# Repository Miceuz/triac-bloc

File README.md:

triac-bloc
==========

Version 3 plan:
* use fl5150mx
* rs845
* filtering and protection 

A universal power block based on triac. In essence this is a solid state relay that can be augmented with some bells and whistles. 

Bells and whistles:
 * Attiyny44 MCU on board
 * I2C interface
 * Optional filtering
 * Optional snubber network
 * maximum power - 6kW
 * zero crossing detection
 * firmware supprots linear output power control
 * phase shift dimmer mode
 * switch at zero-crossing mode
 * “low level” zero-crossing signal output
 * “low level” triac trigger signal input
 * 4 spare MCU pins available for additional features
 * open source hardware and firmware

More info available at: http://wemakethings.net/2013/10/27/triac-bloc/

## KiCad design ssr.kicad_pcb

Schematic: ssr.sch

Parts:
C1: 10nF 400V; C_Rect_L13_W4_P10; PartNo R46KF210050N0K
C2: 47nF 400V; C_Rect_L13_W6_H12_P10; PartNo R46KI24705001K
C3: 100nF 400V; C_Rect_L13_W6_H12_P10; PartNo BFC233922104
C4: 1u; C_0603; PartNo ?
C5: 100uF; Elko_vert_11.2x7.5mm_RM2.5_CopperClear; PartNo ?
C6: C; C_0603; PartNo ?
C7: 10u; Elko_vert_11.2x7.5mm_RM2.5_CopperClear; PartNo ?
C8: 1n; c_0603; PartNo ?
C9: 1u; C_0603
CON1: AVR-ISP-6; Pin_Header_Straight_2x03_Pitch2.54mm; PartNo ?
CONN10: CONN_01X06; Pin_Header_Straight_1x06_Pitch2.54mm; PartNo ?
D1, D2: LED; SM0805; PartNo ?
D3, D5, D6, D7: 1N4148; SOD-323; PartNo ?
D4: 1N4148; SOD-323; PartNo 1N4148WS
F1: FUSE; Fuseholder5x20_horiz_open_universal_Type-III; PartNo 0314030.MXP
IC2: ATTINY441-SSU; SOIC-14_3.9x8.7mm_Pitch1.27mm; PartNo ATTINY441-SSU
J1: 240VAC; Molex_MiniFit-JR-5556-02A_2x01x4.20mm_Straight; PartNo ?
J2: LOAD; Molex_MiniFit-JR-5556-02A_2x01x4.20mm_Straight; PartNo ?
L1: 40-100uH; Choke_Toroid_8x16mm_Vertical; PartNo ?
P1, P6: CONN_4; connect-SC-04; PartNo ?
Q1, Q2: 2N3904; sot23; PartNo MMBT3904-7-F
R1: 360R; R15.5x6; PartNo CFR200J390R
R2: 4.7k; r_0603; PartNo ?
R3: 39; RC05; PartNo MFP1-39R JI
R4, R15: 1k; r_0603; PartNo ?
R5: 22k; r_0603; PartNo ?
R6: 470R; R12x5.2; PartNo CFR100J470R
R7, R9: 10k; r_0603; PartNo ?
R8: 510k; RC05; PartNo MF50 510K
R10: 200; r_0603; PartNo ?
R11, R12: 220; r_0603; PartNo ?
R13, R14: 220k; r_2010; PartNo MCPWR10FTEQ2203
R16: 0R; r_0603; PartNo ?
R17: 120; r_0603; PartNo ?
U1: MOC-3052; optocoupler-2-DIL06; PartNo MOC3052M
U2: BTA41; top3; PartNo BTA41-600BRG
U3: 4N35; mdip_6; PartNo 4N35S-M..
U4: SP3485EN; SOIC-8_3.9x4.9mm_Pitch1.27mm; PartNo SP485EMN-L
VR1: VR; varistor-S05K40; PartNo MCSR431K07DS

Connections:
/FIRE: U1.4 (S2), U2.3
/LINE: F1.1, R3.2, R6.2, R13.2, U2.2, VR1.1
/LOAD: C1.2, C2.2, L1.1, U2.1
/LOAD-FILTERED: C3.2, J2.1, L1.2, R8.2
/MISO: CON1.1, IC2.8 ((PCINT5/MISO/TXD1/T2/TOCC4/ACO0/ADC5)PA5), R12.1
/MOSI: CON1.4, IC2.7 ((PCINT6/MOSI/SDA/XCK1/TOCC5/ACO1/ADC6)P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), R11.1
/NEUTRAL: J1.2, J2.2, R14.2, VR1.2
/RESET: CON1.5, IC2.4 ((PCINT11/dW/~RESET~/ADC9)PB3), R7.1
/RS485-A: P6.3, R16.1, U4.6 (A)
/RS485-B: P6.2, R17.2, U4.7 (B)
/RX: IC2.5 ((PCINT10/RXD0/ICP2/CLKO/TOCC7/ADC8)PB2), U4.1 (RO)
/SCK: CON1.3, IC2.9 ((PCINT4/SCK/SCL/RXD1/T1/TOCC3/AIN11/ADC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), U4.2 (~RE~), U4.3 (DE)
/TX: IC2.6 ((PCINT7/~SS~/TXD0/ICP1/TOCC6/ADC7)PA7), U4.4 (DI)
GND: C4.2, C5.2, C6.2, C9.2, CON1.6, CONN10.1, D1.2 (K), D2.2 (K), IC2.14 (GND), P1.1, P6.4, Q1.3 (E), R9.2, U3.4, U4.5 (GND)
unnamed: C1.1, R3.1
unnamed: C2.1, R1.2, R6.1
unnamed: C3.1, F1.2, J1.1, R8.1
unnamed: C7.1, D4.1 (K), D5.1 (K), R4.2, R5.2
unnamed: C7.2, D3.2 (A), Q2.3 (E)
unnamed: C8.1, D4.2 (A), D7.1 (K), R13.1
unnamed: C8.2, D5.2 (A), D6.1 (K), R14.1
unnamed: CONN10.2, IC2.10 ((PCINT3/SCK/XCK0/T0/TOCC2/AIN10/ADC3)PA3)
unnamed: CONN10.3, IC2.11 ((PCINT2/~SS~/RXD0/TOCC1/AIN01/ADC2)PA2)
unnamed: CONN10.4, IC2.12 ((PCINT1/MOSI/TXD0/TOCC0/AIN00/ADC1)PA1)
unnamed: CONN10.5, IC2.13 ((PCINT0/MISO/AREF/ADC0)PA0)
unnamed: D1.1 (A), R12.2
unnamed: D2.1 (A), R11.2
unnamed: D3.1 (K), D6.2 (A), D7.2 (A), Q2.1 (B), R5.1
unnamed: Q1.1 (B), R15.2
unnamed: Q1.2 (C), R10.2
unnamed: Q2.2 (C), U3.2
unnamed: R1.1, U1.6 (S1)
unnamed: R4.1, U3.1
unnamed: R10.1, U1.2 (K)
unnamed: R16.2, R17.1
ON: IC2.2 ((PCINT8/CLKI/XTAL1/ADC11)PB0), P1.3, R9.1, R15.1
VCC: C4.1, C5.1, C6.1, C9.1, CON1.2, CONN10.6, IC2.1 (VCC), P1.2, P6.1, R2.2, R7.2, U1.1 (A), U4.8 (VCC)
ZERO_CROSSING: IC2.3 ((PCINT9/INT0/XTAL2/ADC10)PB1), P1.4, R2.1, U3.5

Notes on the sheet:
TODO: move ON signal to another pin, ICP is cool for capturing timer
R = 340V / 1A -------------------- (1A - opto triac max surge current)
Zerro Cossing circuit by Dego http://www.dextrel.net/diyzerocrosser.htm
Saugiklio laikiklis: MFG:Littelfuse Inc. 01220090Z FUSE CLIP CARTRIDGE 250V 30A PCB Digikey/F4190-ND Farnell/1608255 0.87€

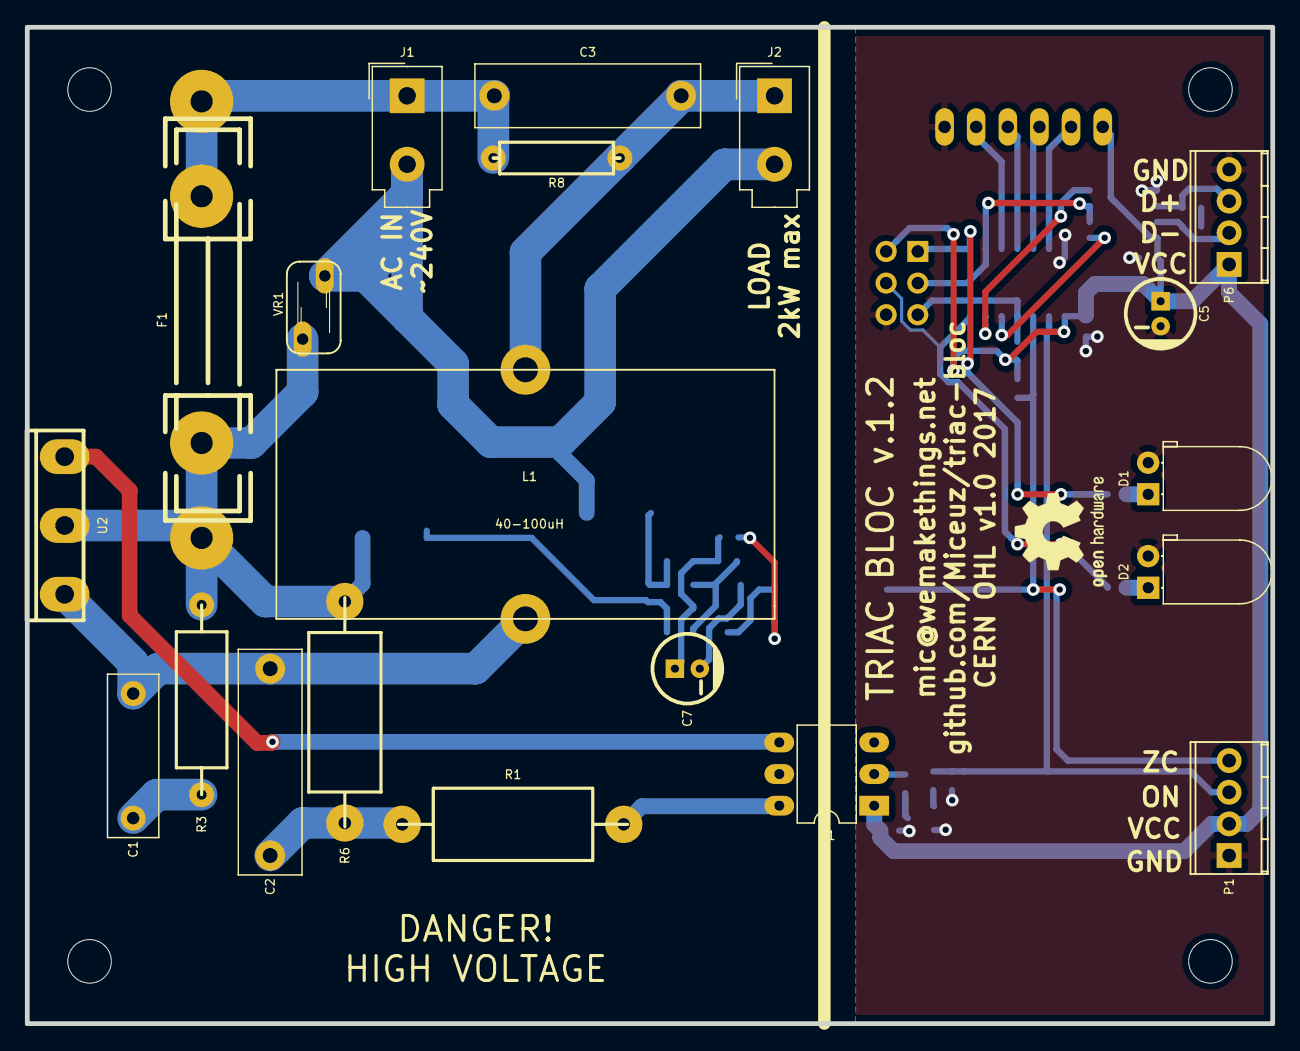
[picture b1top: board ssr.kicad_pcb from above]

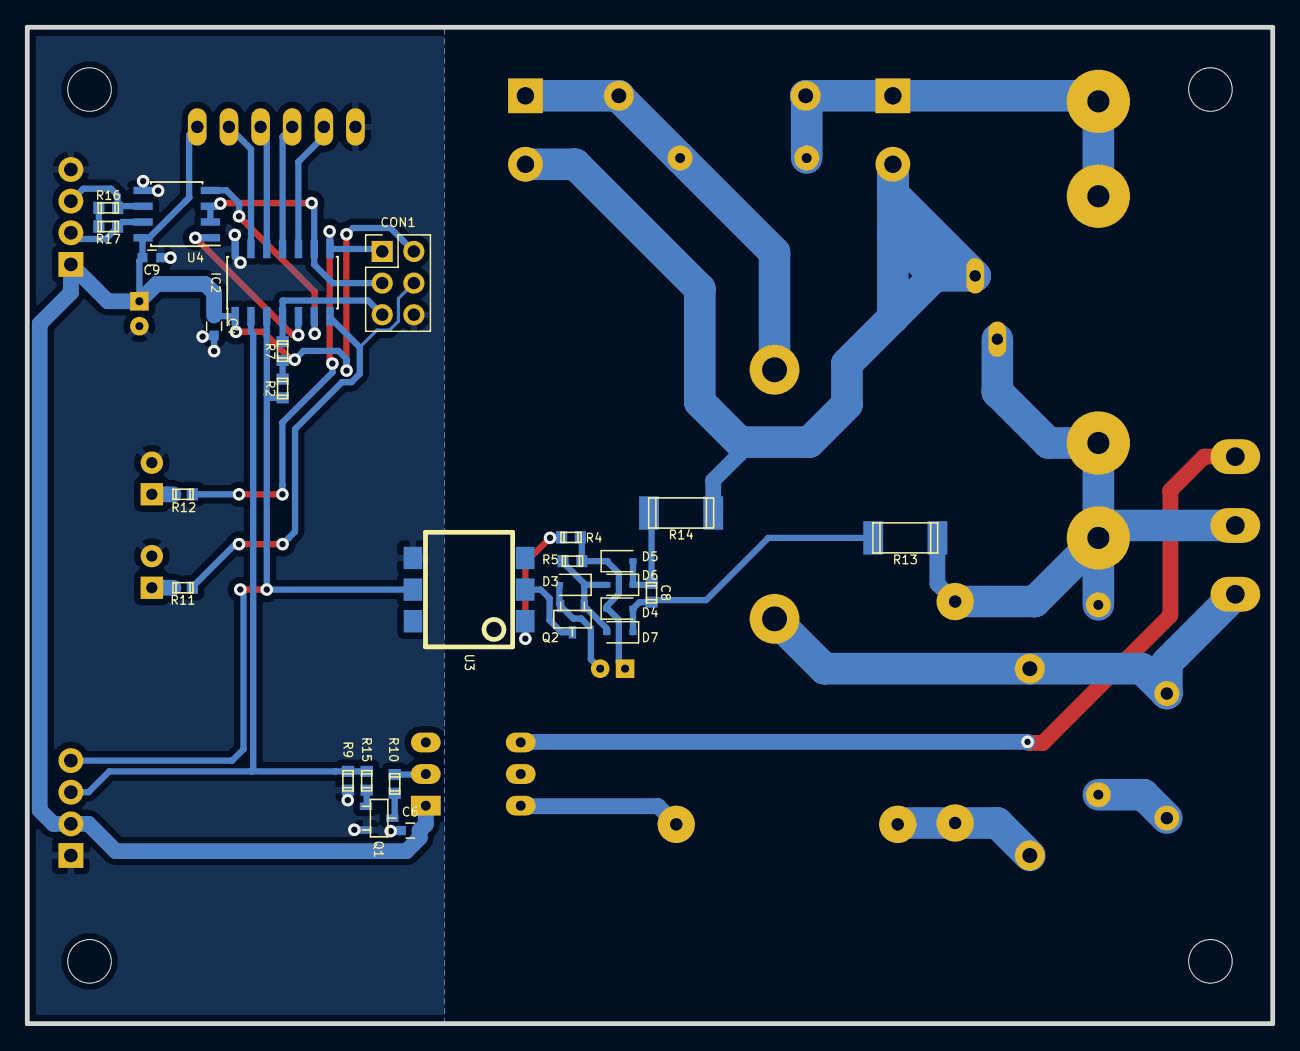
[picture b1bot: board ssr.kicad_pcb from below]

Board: 2 copper layers, 100.0 x 80.0 mm, 49 parts (28 on the bottom side), 38 nets.

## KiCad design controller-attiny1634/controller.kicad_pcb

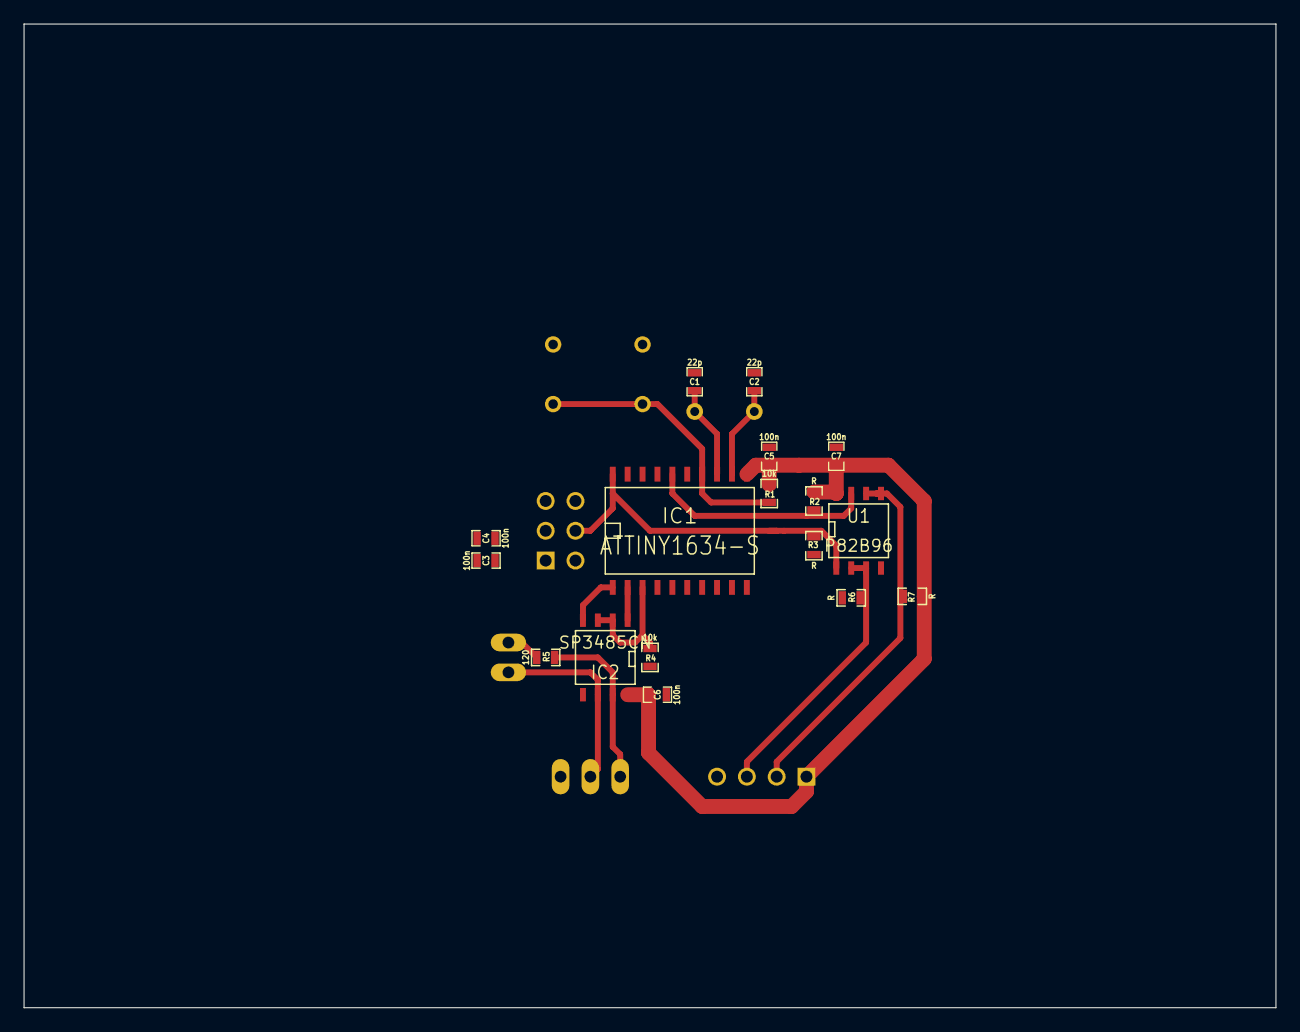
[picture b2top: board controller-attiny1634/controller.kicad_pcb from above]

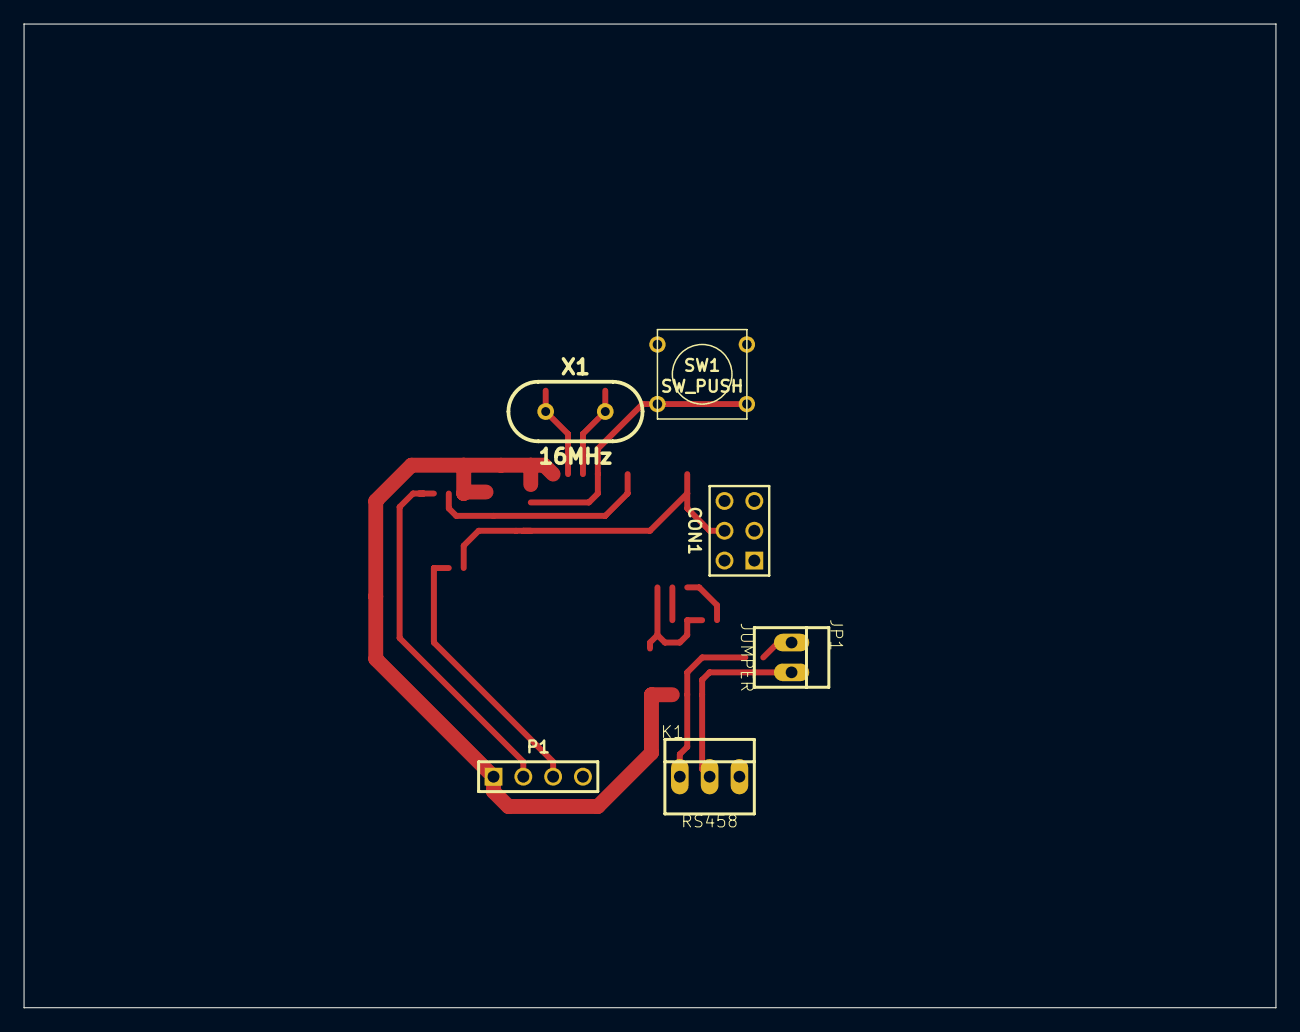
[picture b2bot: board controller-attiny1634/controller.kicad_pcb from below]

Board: 2 copper layers, 106.7 x 83.8 mm, 23 parts (6 on the bottom side), 16 nets.

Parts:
C1, C2: 22p; SM0603_Capa
C3, C4, C5, C6, C7: 100n; SM0603_Capa
CON1: AVR-ISP-6; pin_array_3x2
IC1: ATTINY1634-S; SO20L
IC2: SP3485CN; SO8N
JP1: JUMPER; PINHEAD1-2
K1: RS458; PINHEAD1-3
P1: I2C; PIN_ARRAY_4x1
R1, R4: 10k; SM0603_Resistor
R2, R3, R6, R7: R; SM0603_Resistor
R5: 120; SM0603_Resistor
SW1: SW_PUSH; SW_PUSH_SMALL
U1: P82B96; SO8N
X1: 16MHz; HC-49V

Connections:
/MISO: CON1.1, IC1.19
/MODBUS_A: IC2.6, JP1.2, K1.2
/MODBUS_B: IC2.7, K1.1, R5.2
/RESET: CON1.5, IC1.14, R1.2, SW1.2
/SCL: CON1.3, IC1.16, R2.2, U1.7
/SCL_OUT: P1.2, R7.2, U1.5, U1.6
/SDA: CON1.4, IC1.20, R3.2, U1.1
/SDA_OUT: P1.3, R6.2, U1.2, U1.3
GND: C1.1, C2.1, C3.2, C4.1, C5.1, C6.1, C7.1, CON1.6, IC1.10, IC2.5, K1.3, P1.4, R4.2, SW1.1, U1.4
unnamed: C1.2, IC1.13, X1.2
unnamed: C2.2, IC1.12, X1.1
unnamed: IC1.2, IC2.1
unnamed: JP1.1, R5.1
unnamed: IC1.3, IC2.2, IC2.3, R4.1
unnamed: IC1.1, IC2.4
VCC: C3.1, C4.2, C5.2, C6.2, C7.2, CON1.2, IC1.11, IC2.8, P1.1, R1.1, R2.1, R3.1, R6.1, R7.1, U1.8

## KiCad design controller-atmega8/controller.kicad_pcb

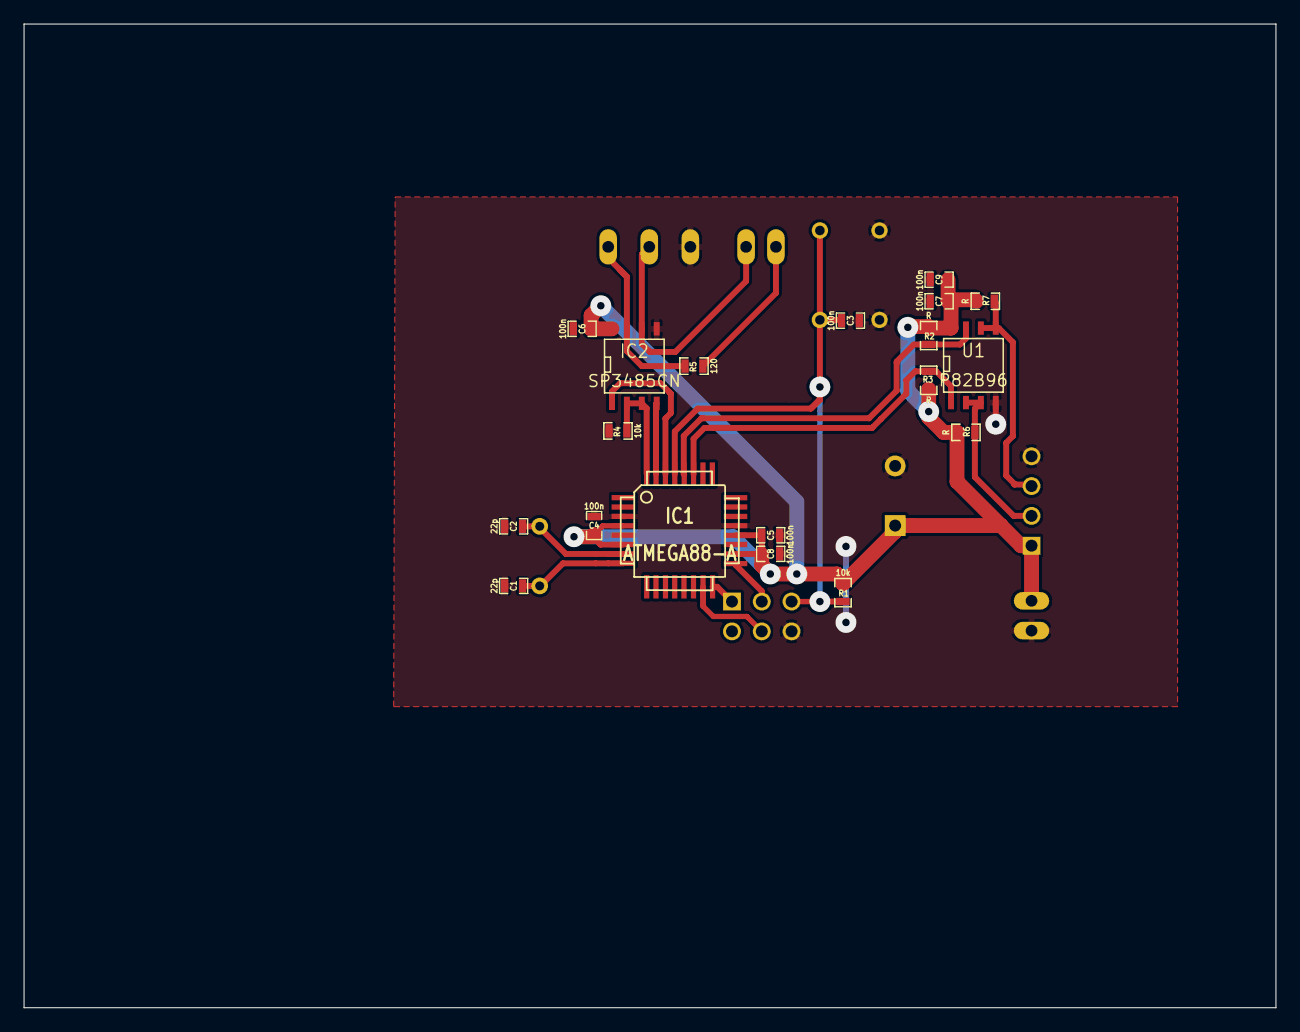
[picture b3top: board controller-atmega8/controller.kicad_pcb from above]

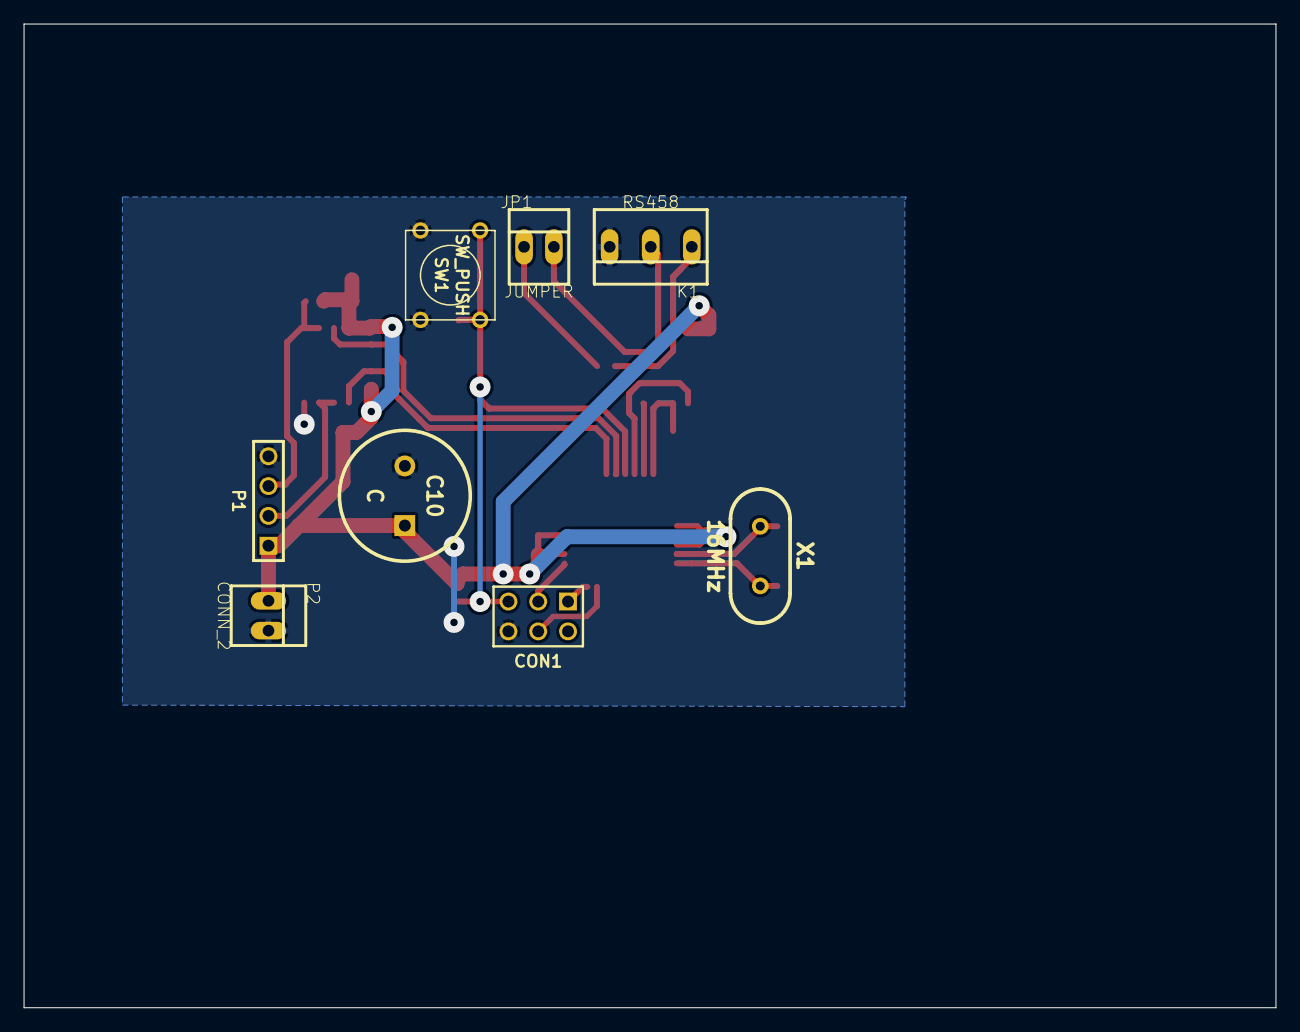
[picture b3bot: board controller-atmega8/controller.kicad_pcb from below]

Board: 2 copper layers, 106.7 x 83.8 mm, 27 parts (8 on the bottom side), 18 nets.

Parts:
C1, C2: 22p; SM0603_Capa
C3, C4, C5, C6, C7, C8, C9: 100n; SM0603_Capa
C10: C; C2V10
CON1: AVR-ISP-6; pin_array_3x2
IC1: ATMEGA88-A; TQFP32
IC2: SP3485CN; SO8N
JP1: JUMPER; PINHEAD1-2
K1: RS458; PINHEAD1-3
P1: I2C; PIN_ARRAY_4x1
P2: CONN_2; PINHEAD1-2
R1, R4: 10k; SM0603_Resistor
R2, R3, R6, R7: R; SM0603_Resistor
R5: 120; SM0603_Resistor
SW1: SW_PUSH; SW_PUSH_SMALL
U1: P82B96; SO8N
X1: 16MHz; HC-49V

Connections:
/DRIVER_ENABLE: IC1.32, IC2.2, IC2.3, R4.1
/MISO: CON1.1, IC1.16
/MODBUS_A: IC2.6, JP1.2, K1.2
/MODBUS_B: IC2.7, K1.1, R5.2
/MOSI: CON1.4, IC1.15
/RESET: C3.1, CON1.5, IC1.29, R1.2, SW1.2
/SCK: CON1.3, IC1.17
/SCL: IC1.28, R2.2, U1.7
/SCL_OUT: P1.3, R7.2, U1.5, U1.6
/SDA: IC1.27, R3.2, U1.1
/SDA_OUT: P1.2, R6.2, U1.2, U1.3
GND: C1.1, C2.1, C3.2, C4.1, C5.1, C6.1, C7.1, C8.1, C9.1, C10.2, CON1.6, IC1.3, IC1.5, IC1.21, IC2.5, K1.3, P1.4, P2.2, R4.2, SW1.1, U1.4
unnamed: IC1.30, IC2.1
unnamed: IC1.31, IC2.4
unnamed: C2.2, IC1.7, X1.1
unnamed: C1.2, IC1.8, X1.2
unnamed: JP1.1, R5.1
VCC: C4.2, C5.2, C6.2, C7.2, C8.2, C9.2, C10.1, CON1.2, IC1.4, IC1.6, IC1.18, IC1.20, P1.1, P2.1, R1.1, R2.1, R3.1, R6.1, R7.1, U1.8

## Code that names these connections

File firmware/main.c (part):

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#include <avr/eeprom.h>
#include "usiTwiSlave.h"

#define GREEN PB0
#define RED PB1

/*
 * Sets the linear output power in dimmer mode. 1 byte argument: [0 - 255]
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}

inline void conductionOn() {
	PORTA |= _BV(PA7);
}

inline void conductionOff() {
	PORTA &= ~_BV(PA7);
}

inline void resetTimer() {
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 * Manual mode is detected if MOSI/SDA pin is shorted to ground
 * */
static uint8_t isManualMode() {
        DDRA &= ~_BV(PA6);
        PORTA |= _BV(PA6);
        asm("nop");
        uint8_t isManualMode = !(PINA & _BV(PA6));
        PORTA &= ~_BV(PA6);
        return isManualMode;
}

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	MCUSR = 0;
	wdt_disable();
	DDRB |= _BV(RED) | _BV(GREEN);
	PORTB |= _BV(PB2); //zc pullup

	DDRA |= _BV(PA7);  //fire output
	PORTA = 0;

        if(isManualMode()) {
                //pot is expected to be connected to
                //1 GND
                //2 PA2/ADC2 - wiper
                //3 PA0
                DDRA |= _BV(PA0);
                PORTA |= _BV(PA0); //set up high level on PA0 for positive pot leg
                
                ADMUX = 2;
                ADCSRA = _BV(ADEN) | _BV(ADPS2);
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			ledOff(RED);
			_delay_ms(100);
		}
                //~ if(PINA & _BV(PA6)) {
                        //~ ledOn(GREEN);
                //~ } else {
                        //~ ledOff(GREEN);
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
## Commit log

2013-04-24 one more rearrangement of parts creepage distances taken care of homogenized via sizes part names and values taken care of
2013-04-26 this commit is a mess
2013-05-07 boards sent for manufacture
2013-06-10 initial firmware
2013-06-22 if tx buffer is empty and byte was requested, return 0 so not to block.
2013-06-22 u visko daug
2013-06-22 power output linearization
2013-10-27 some work on firmware, experiments, some documentation has been added
2013-11-25 ignore more
2013-11-25 everything works pretty well, I've already forgot what the changes are.
2013-11-25 everything there is to
2013-11-27 relay mode. commit before test
2013-11-27 just a small fix
2014-01-20 add schematics in PDF for people without Kicad
2014-05-18 use expansion header to set I2C address
2014-05-18 if MOSI is grounded on boot, switch to manual control, expect a potentiometer wiper connected to PA2, HIGH logic level switched on PA0, this way 200" picth pot can be hooked up directly to expansion 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
2014-06-02 Add image
2014-12-23 remove hex from repo
2015-11-01 Change ZC detection subcircuit to a more efficient one, add BOM data to schematics, Also a new kicad
2015-11-01 Remove some junk
2017-08-22 Change MCU to attiny441, add rs485, change board dimensions to half-euro-pannel, change leds to THT, change connectors, total reroute
2017-09-29 Shuffle silkscreen around, order the boards made
2019-06-10 Scribble an idea here
2020-02-18 KiCad library change, export PDF schematics

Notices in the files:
ssr.kicad_pcb:
CERN OHL v1.0 2017
